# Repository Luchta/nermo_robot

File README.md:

# nermo_robot
 Hardware repository with all necessary files to build the NeRmo robot.

## DISCLAIMER

 This submission is to be used within the general terms of service of the Human Brain Project (HBP). In particular, users should not download the following code if they intend to make a military use of it.

## Repository Structure
* 3D Printing
	* STL_Files
	* Parts List
* Electronics
	* Eagle Files
	* Parts List
* Nermo User Manual.pdf
* README.md
* LICENSE

## License
[GPLv3](https://fsf.org/)

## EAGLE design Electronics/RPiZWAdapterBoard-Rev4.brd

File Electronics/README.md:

# nermo_robot
 Electronics Subfolder

## Custom PCBs

* LegSensorBoard
* RPiZWAdapterBoard
* ServoBoard
* Wire_Distr

## License
[GPLv3](https://fsf.org/)

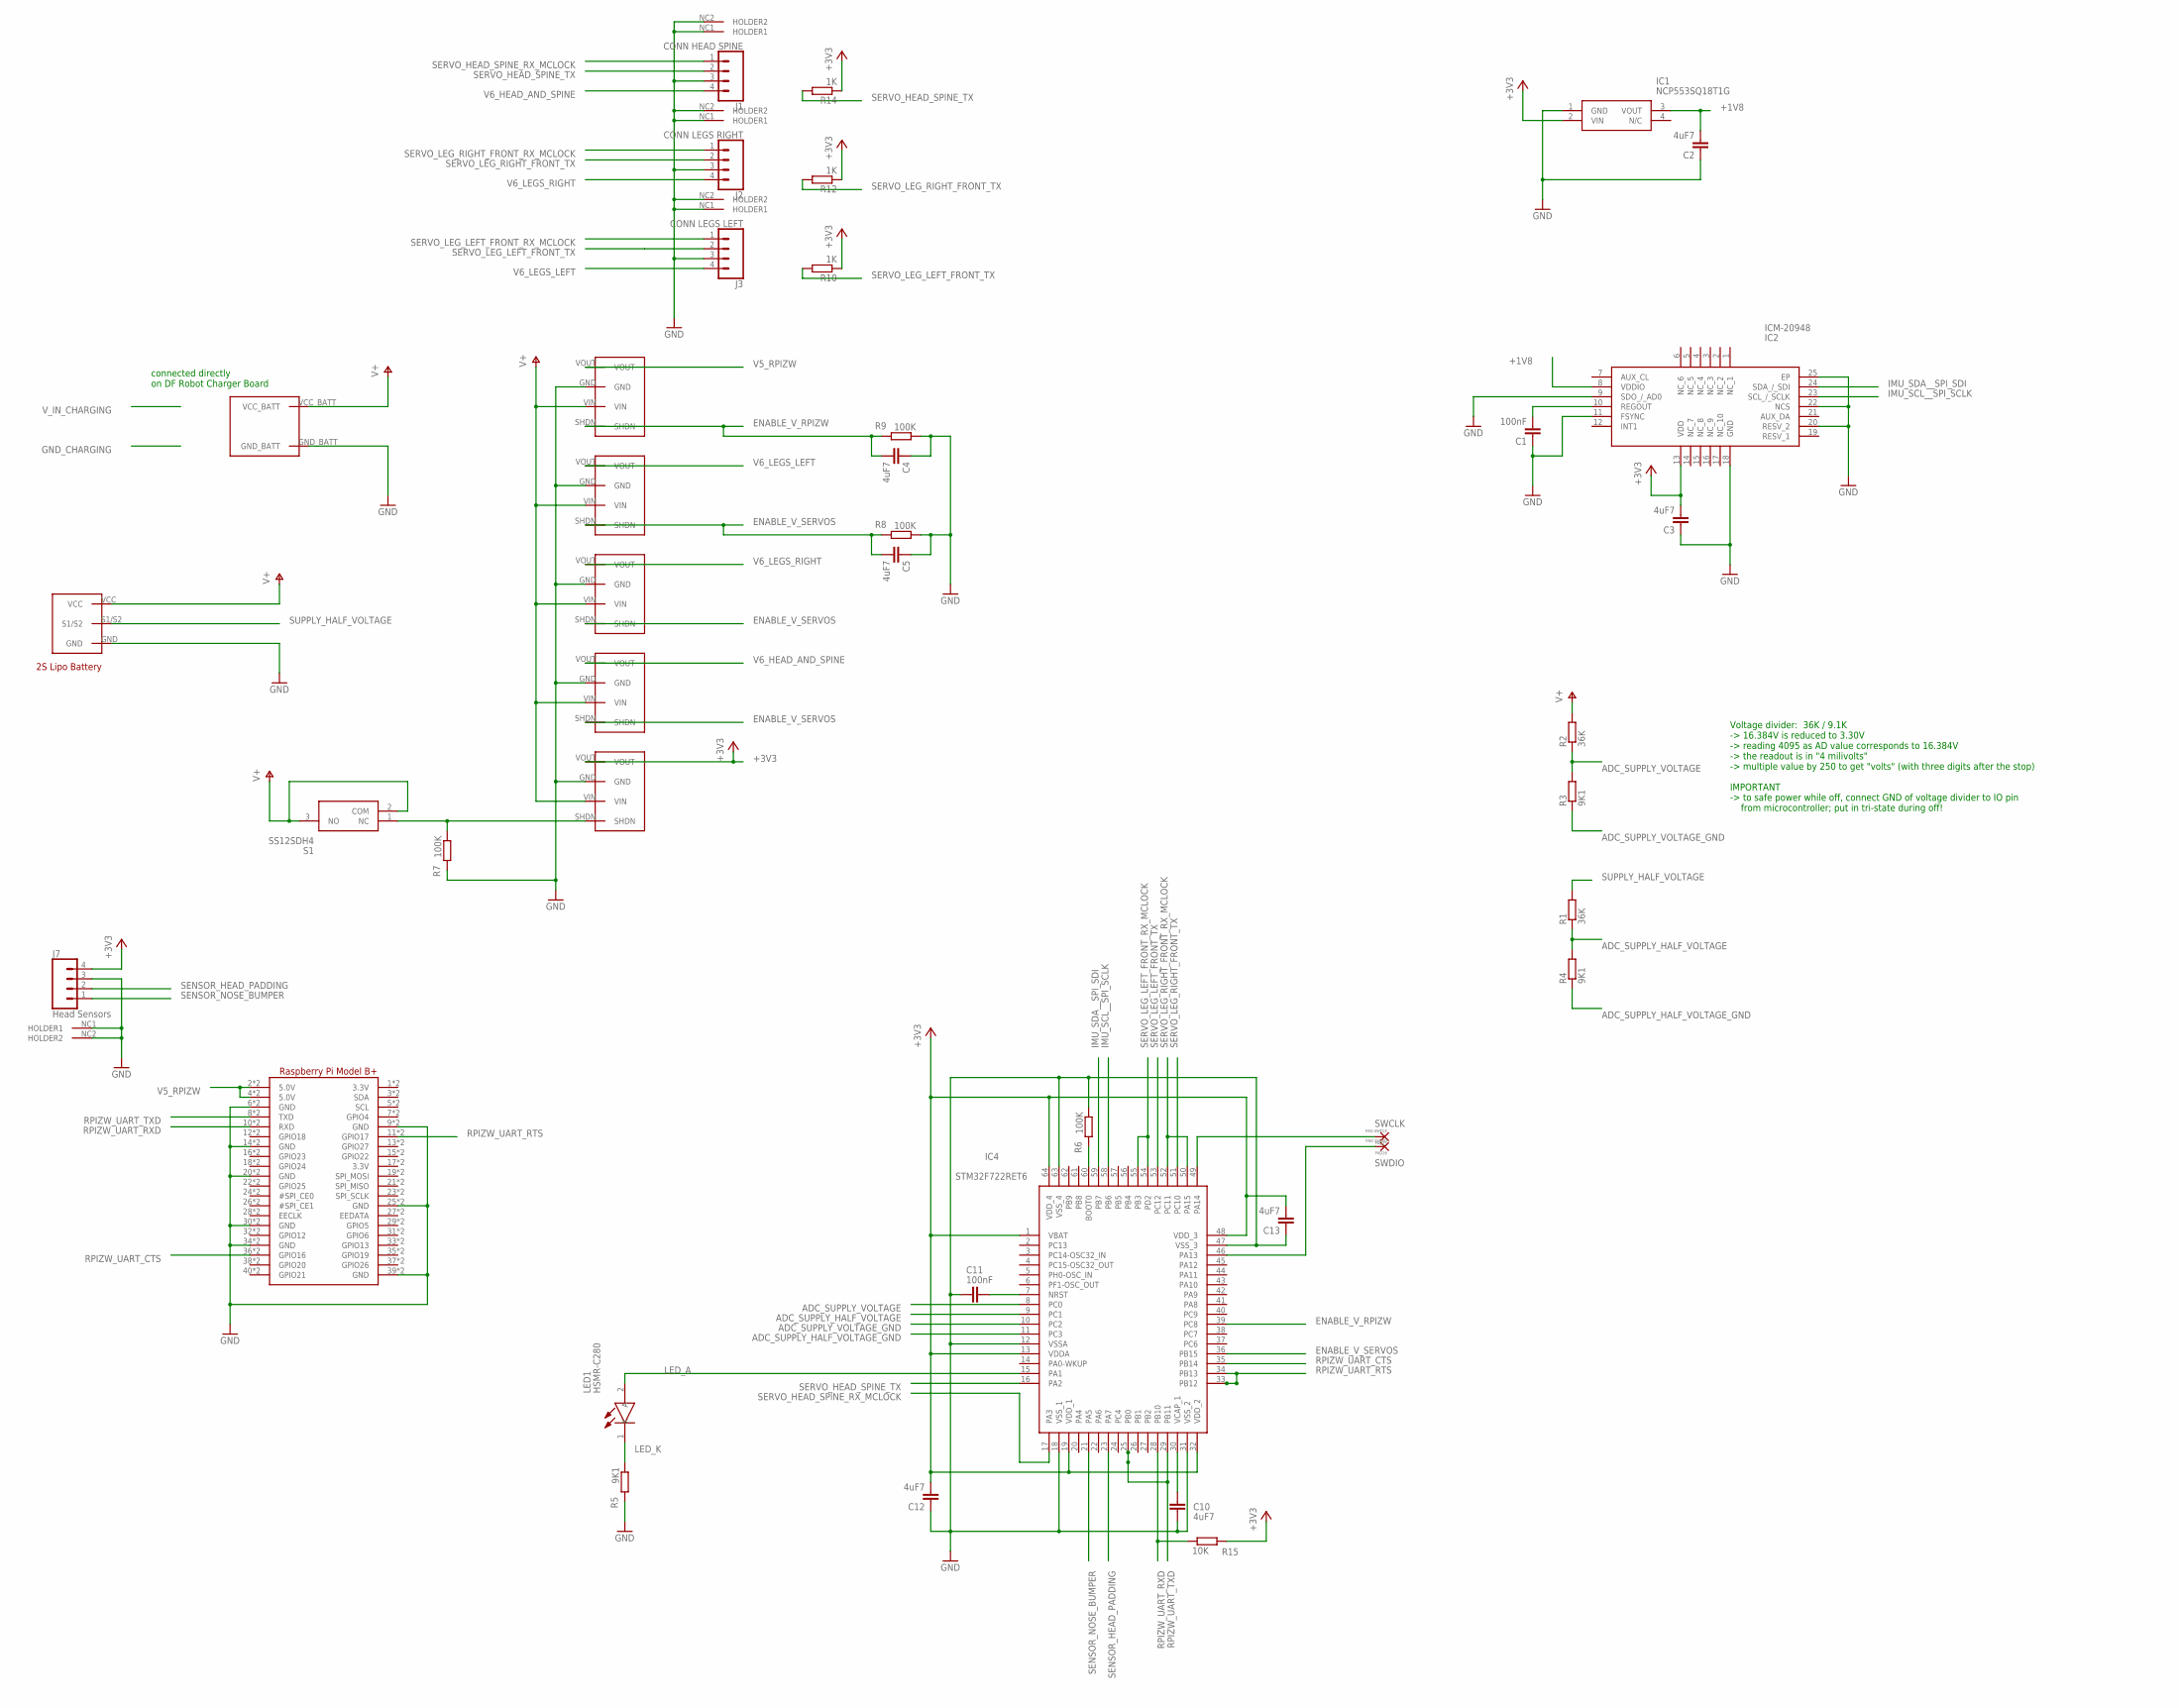
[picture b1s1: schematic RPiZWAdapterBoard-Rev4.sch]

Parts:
C1, C11: 100nF; C0402
C2, C3, C4, C5, C10, C12, C13: 4uF7; C0402
IC1: NCP553SQ18T1G; NCP563SQ18T1G
IC2: ICM-20948; QFN40P300X300X105-25N
IC4: STM32F722RET6; QFP50P1200X1200X160-64N
J1: CONN HEAD SPINE; JST04_SH_1MM
J2: CONN LEGS RIGHT; JST04_SH_1MM
J3: CONN LEGS LEFT; JST04_SH_1MM
J7: Head Sensors; JST04_SH_1MM
LED1: HSMR-C280; LEDC1005X50N
PAD25: PAD SWCLK; SMD12X08
PAD26: PAD SWDIO; SMD12X08
R1, R2: 36K; R0402
R3, R4, R5: 9K1; R0402
R6, R7, R8, R9: 100K; R0402
R10, R12, R14: 1K; R0402
R15: 10K; R0402
RPI1: MICROBUILDER_RASPBERRYPI_BPLUSWIDE; MICROBUILDER_PI_BONNET_THMSMT_WIDE
S1: SS12SDH4
U$1, U$3, U$4, U$5, U$6: POLOLU_REGULATOR
U$7: JST-S3B-XH-A_BATTCON; JST-S3B-XH-A
U$8: DFROBOT_CHARGER_CUTOUTNARROW; DFROBOT_CHARGER_CUTOUT_NARROW

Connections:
+1V8: C2.2, IC1.3 (VOUT), IC2.8 (VDDIO)
+3V3: C3.2, C12.2, C13.2, IC1.2 (VIN), IC2.13 (VDD), IC4.1 (VBAT), IC4.13 (VDDA), IC4.19 (VDD_1), IC4.32 (VDD_2), IC4.48 (VDD_3), IC4.64 (VDD_4), J7.4, R10.1, R12.1, R14.1, R15.2, U$6.VOUT
ADC_SUPPLY_HALF_VOLTAGE: IC4.9 (PC1), R1.1, R4.2
ADC_SUPPLY_HALF_VOLTAGE_GND: IC4.11 (PC3), R4.1
ADC_SUPPLY_VOLTAGE: IC4.8 (PC0), R2.1, R3.2
ADC_SUPPLY_VOLTAGE_GND: IC4.10 (PC2), R3.1
ENABLE_V_RPIZW: C4.2, IC4.39 (PC8), R9.2, U$1.SHDN
ENABLE_V_SERVOS: C5.2, IC4.36 (PB15), R8.2, U$3.SHDN, U$4.SHDN, U$5.SHDN
GND: C1.1, C2.1, C3.1, C4.1, C5.1, C10.1, C11.2, C12.1, C13.1, IC1.1 (GND), IC2.9 (SDO_/_AD0), IC2.11 (FSYNC), IC2.18 (GND), IC2.20 (RESV_2), IC2.22 (NCS), IC2.25 (EP), IC4.12 (VSSA), IC4.18 (VSS_1), IC4.31 (VSS_2), IC4.47 (VSS_3), IC4.63 (VSS_4), J1.3, J1.NC1 (HOLDER1), J1.NC2 (HOLDER2), J2.3, J2.NC1 (HOLDER1), J2.NC2 (HOLDER2), J3.3, J3.NC1 (HOLDER1), J3.NC2 (HOLDER2), J7.3, J7.NC1 (HOLDER1), J7.NC2 (HOLDER2), R5.2, R6.1, R7.2, R8.1, R9.1, RPI1.6 (GND), RPI1.9 (GND), RPI1.14 (GND), RPI1.20 (GND), RPI1.25 (GND), RPI1.30 (GND), RPI1.34 (GND), RPI1.39 (GND), RPI1.S6 (GND), RPI1.S9 (GND), RPI1.S14 (GND), RPI1.S20 (GND), RPI1.S25 (GND), RPI1.S30 (GND), RPI1.S34 (GND), RPI1.S39 (GND), U$1.GND, U$3.GND, U$4.GND, U$5.GND, U$6.GND, U$7.GND, U$8.GND_BATT
IMU_SCL__SPI_SCLK: IC2.23 (SCL_/_SCLK), IC4.58 (PB6)
IMU_SDA__SPI_SDI: IC2.24 (SDA_/_SDI), IC4.59 (PB7)
LED_A: IC4.15 (PA1), LED1.2 (A)
LED_K: LED1.1 (K), R5.1
unnamed: R7.1, S1.1 (NC), U$6.SHDN
unnamed: C1.2, IC2.10 (REGOUT)
unnamed: IC4.60 (BOOT0), R6.2
unnamed: C11.1, IC4.7 (NRST)
unnamed: C10.2, IC4.30 (VCAP_1)
RPIZW_UART_CTS: IC4.35 (PB14), RPI1.36 (GPIO16), RPI1.S36 (GPIO16)
RPIZW_UART_RTS: IC4.33 (PB12), IC4.34 (PB13), RPI1.11 (GPIO17), RPI1.S11 (GPIO17)
RPIZW_UART_RXD: IC4.28 (PB10), R15.1, RPI1.10 (RXD), RPI1.S10 (RXD)
RPIZW_UART_TXD: IC4.25 (PB0), IC4.29 (PB11), RPI1.8 (TXD), RPI1.S8 (TXD)
SENSOR_HEAD_PADDING: IC4.23 (PA7), J7.2
SENSOR_NOSE_BUMPER: IC4.21 (PA5), J7.1
SERVO_HEAD_SPINE_RX_MCLOCK: IC4.17 (PA3), J1.1
SERVO_HEAD_SPINE_TX: IC4.16 (PA2), J1.2, R14.2
SERVO_LEG_LEFT_FRONT_RX_MCLOCK: IC4.54 (PD2), IC4.55 (PB3), J3.1
SERVO_LEG_LEFT_FRONT_TX: IC4.53 (PC12), J3.2, R10.2
SERVO_LEG_RIGHT_FRONT_RX_MCLOCK: IC4.50 (PA15), IC4.52 (PC11), J2.1
SERVO_LEG_RIGHT_FRONT_TX: IC4.51 (PC10), J2.2, R12.2
SUPPLY_HALF_VOLTAGE: R1.2, U$7.S1/S2
SWCLK: IC4.49 (PA14), PAD25.1
SWDIO: IC4.46 (PA13), PAD26.1
V5_RPIZW: RPI1.2 (5.0V), RPI1.4 (5.0V), RPI1.S2 (5.0V), RPI1.S4 (5.0V), U$1.VOUT
V6_HEAD_AND_SPINE: J1.4, U$5.VOUT
V6_LEGS_LEFT: J3.4, U$3.VOUT
V6_LEGS_RIGHT: J2.4, U$4.VOUT
V+: R2.2, S1.2 (COM), S1.3 (NO), U$1.VIN, U$3.VIN, U$4.VIN, U$5.VIN, U$6.VIN, U$7.VCC, U$8.VCC_BATT

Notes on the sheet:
Voltage divider: 36K / 9.1K -> 16.384V is reduced to 3.30V -> reading 4095 as AD value corresponds to 16.384V -> the readout is in "4 milivolts" -> multiple value by 250 to get "volts" (with three digits after the stop) IMPORTANT -> to safe power while off, connect GND of voltage divider to IO pin 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
connected directly on DF Robot Charger Board

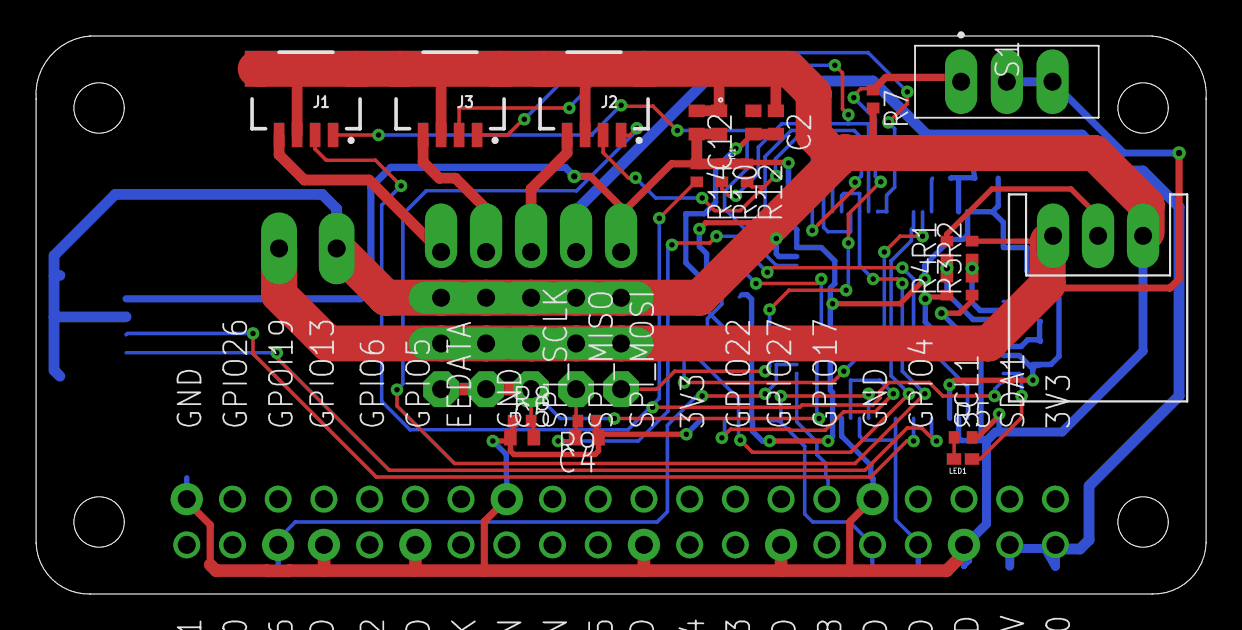
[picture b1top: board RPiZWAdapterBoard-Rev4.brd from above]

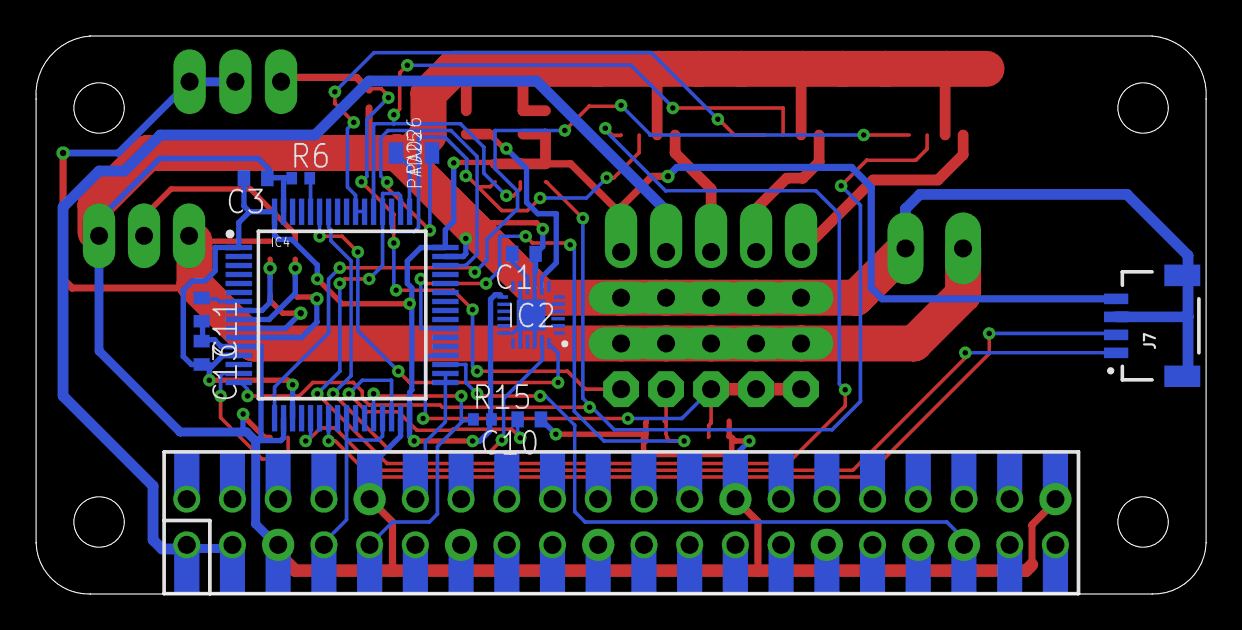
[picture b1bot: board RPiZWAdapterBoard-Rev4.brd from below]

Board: 2 copper layers, 65.0 x 31.0 mm, 41 parts (14 on the bottom side), 38 nets.

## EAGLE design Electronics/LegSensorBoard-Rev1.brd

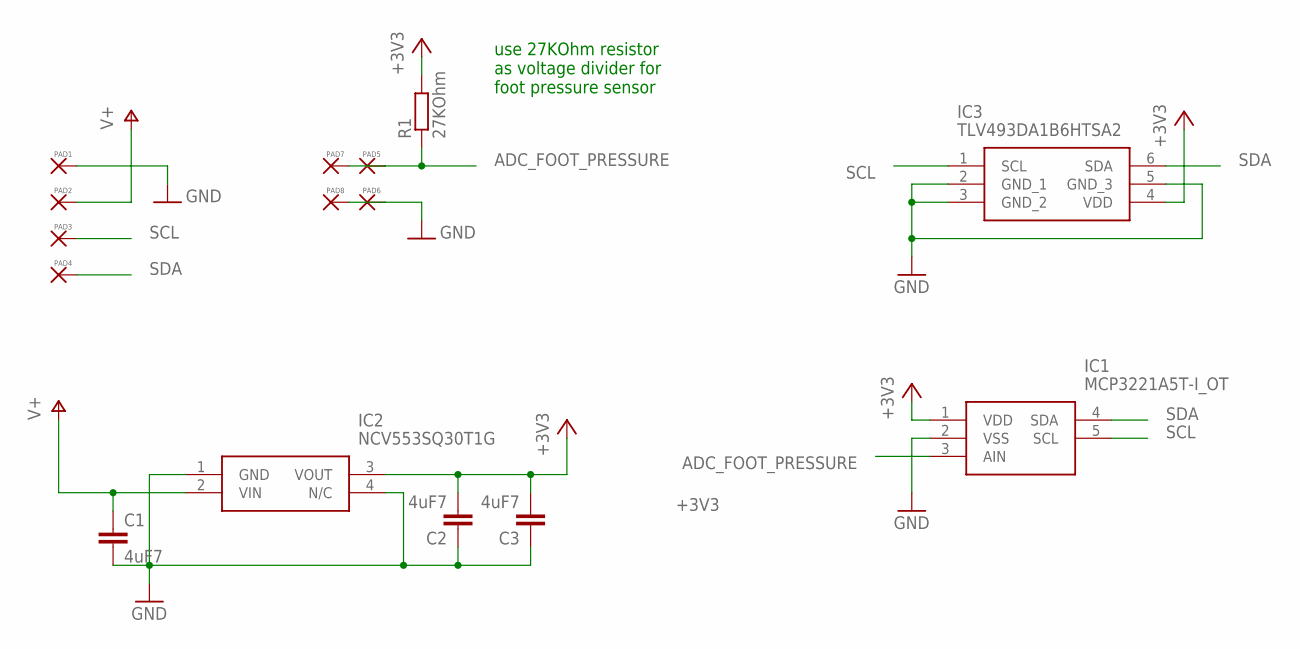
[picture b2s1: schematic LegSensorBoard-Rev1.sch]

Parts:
C1, C2, C3: 4uF7; C0402
IC1: MCP3221A5T-I_OT; SOT95P270X145-5N
IC2: NCV553SQ30T1G; NCP563SQ18T1G
IC3: TLV493DA1B6HTSA2; SOT95P250X110-6N
PAD1, PAD2, PAD3, PAD4: SMD-PAD20X07; SMD20X07
PAD5, PAD6, PAD7, PAD8: SMD-PAD14X08; SMD14X08
R1: 27KOhm; R0402

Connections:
+3V3: C2.2, C3.2, IC1.1 (VDD), IC2.3 (VOUT), IC3.4 (VDD), R1.2
ADC_FOOT_PRESSURE: IC1.3 (AIN), PAD5.1, PAD7.1, R1.1
GND: C1.2, C2.1, C3.1, IC1.2 (VSS), IC2.1 (GND), IC2.4 (N/C), IC3.2 (GND_1), IC3.3 (GND_2), IC3.5 (GND_3), PAD1.1, PAD6.1, PAD8.1
SCL: IC1.5 (SCL), IC3.1 (SCL), PAD3.1
SDA: IC1.4 (SDA), IC3.6 (SDA), PAD4.1
V+: C1.1, IC2.2 (VIN), PAD2.1

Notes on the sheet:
use 27KOhm resistor as voltage divider for foot pressure sensor

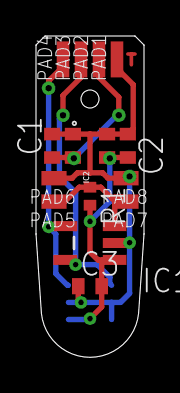
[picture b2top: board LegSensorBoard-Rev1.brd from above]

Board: 2 copper layers, 6.0 x 17.8 mm, 15 parts (1 on the bottom side), 6 nets.

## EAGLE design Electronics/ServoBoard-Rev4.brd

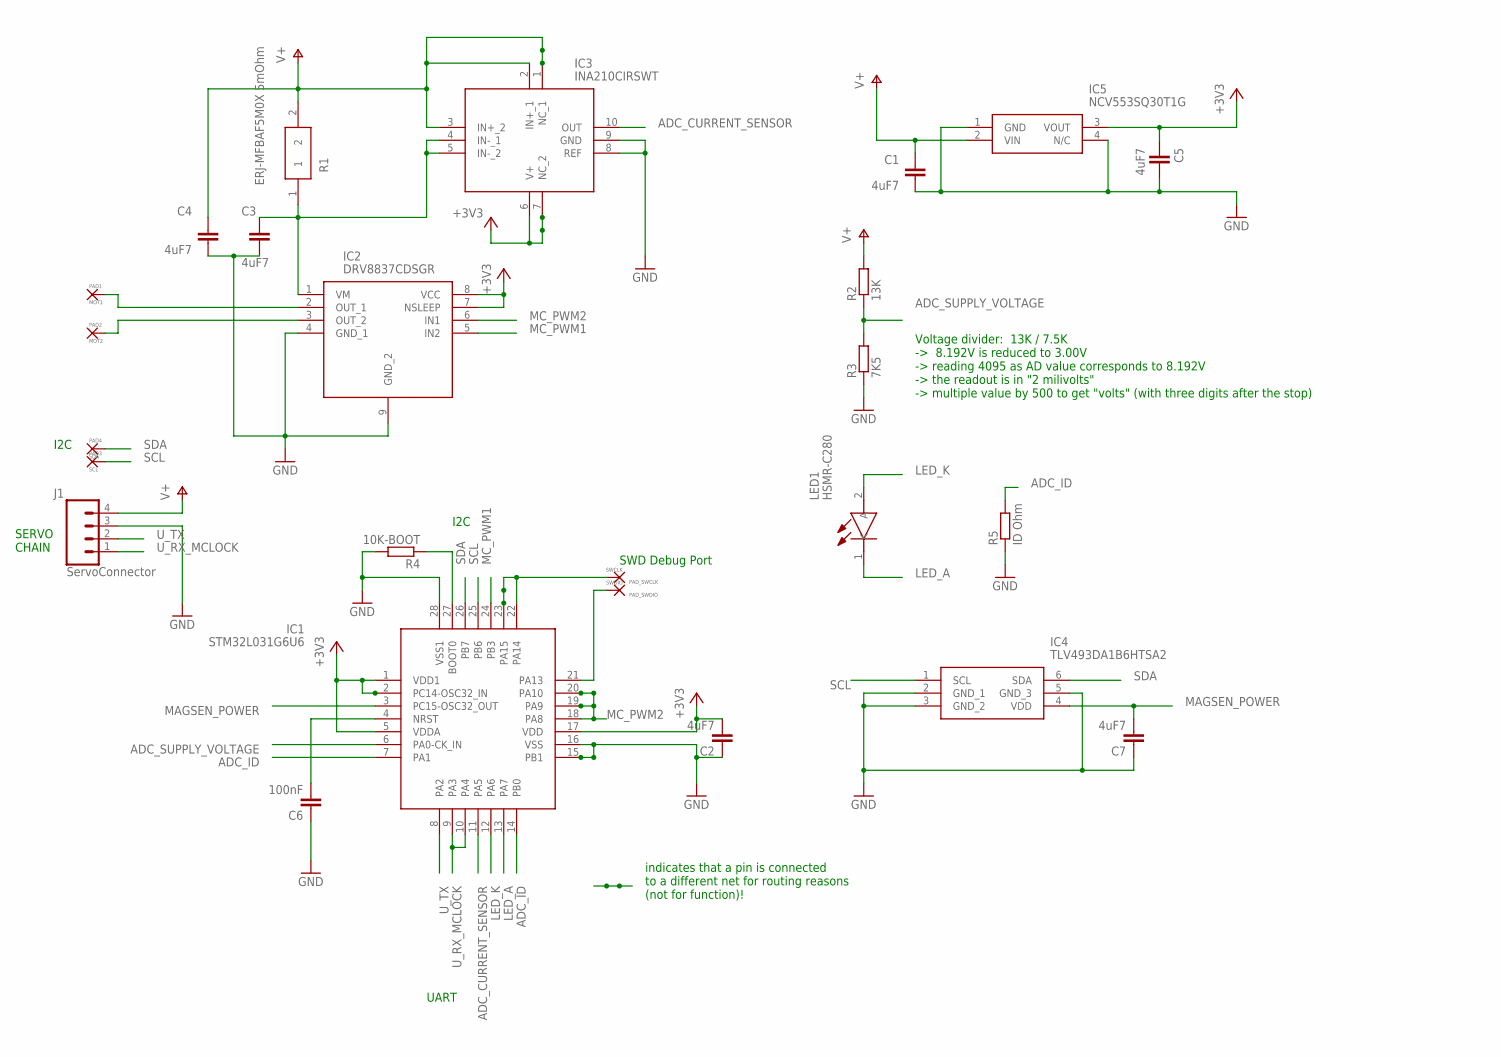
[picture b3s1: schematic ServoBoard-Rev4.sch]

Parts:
C1, C2, C3, C4, C5, C7: 4uF7; C0402
C6: 100nF; C0201
IC1: STM32L031G6U6; QFN50P400X400X60-28N
IC2: DRV8837CDSGR; SON50P200X200X80-9N
IC3: INA210CIRSWT; QFN40P140X180X55-10N
IC4: TLV493DA1B6HTSA2; SOT95P250X110-6N
IC5: NCV553SQ30T1G; NCP563SQ18T1G
J1: ServoConnector; JST04_SH_1MM
LED1: HSMR-C280; LEDC1005X50N
PAD1: MOT1; SMD12X07
PAD2: MOT2; SMD12X07
PAD3: SCL; SMD14X06
PAD4: SDA; SMD14X06
PAD_SWCLK: SWCLK; SMD06X06
PAD_SWDIO: SWDIO; SMD06X06
R1: ERJ-MFBAF5M0X 5mOhm; RESM106X40N
R2: 13K; R0402
R3: 7K5; R0402
R4: 10K-BOOT; R0402
R5: ID Ohm; R0402

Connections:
+3V3: C2.2, C5.1, IC1.1 (VDD1), IC1.2 (PC14-OSC32_IN), IC1.5 (VDDA), IC1.17 (VDD), IC2.7 (NSLEEP), IC2.8 (VCC), IC3.6 (V+), IC3.7 (NC_2), IC5.3 (VOUT)
ADC_CURRENT_SENSOR: IC1.11 (PA5), IC3.10 (OUT)
ADC_ID: IC1.7 (PA1), IC1.14 (PB0), R5.2
ADC_SUPPLY_VOLTAGE: IC1.6 (PA0-CK_IN), R2.1, R3.2
BOOT0: IC1.27 (BOOT0), R4.1
GND: C1.2, C2.1, C3.2, C4.2, C5.2, C6.1, C7.1, IC1.15 (PB1), IC1.16 (VSS), IC1.28 (VSS1), IC2.4 (GND_1), IC2.9 (GND_2), IC3.8 (REF), IC3.9 (GND), IC4.2 (GND_1), IC4.3 (GND_2), IC4.5 (GND_3), IC5.1 (GND), IC5.4 (N/C), J1.3, R3.1, R4.2, R5.1
LED_A: IC1.13 (PA7), LED1.1 (K)
LED_K: IC1.12 (PA6), LED1.2 (A)
MAGSEN_POWER: C7.2, IC1.3 (PC15-OSC32_OUT), IC4.4 (VDD)
MC_PWM1: IC1.24 (PB3), IC2.5 (IN2)
MC_PWM2: IC1.18 (PA8), IC1.19 (PA9), IC1.20 (PA10), IC2.6 (IN1)
MOTOR_1: IC2.2 (OUT_1), PAD1.1
MOTOR_2: IC2.3 (OUT_2), PAD2.1
NRST: C6.2, IC1.4 (NRST)
SCL: IC1.25 (PB6), IC4.1 (SCL), PAD3.1
SDA: IC1.26 (PB7), IC4.6 (SDA), PAD4.1
SWCLK: IC1.22 (PA14), IC1.23 (PA15), PAD_SWCLK.1
SWDIO: IC1.21 (PA13), PAD_SWDIO.1
U_RX_MCLOCK: IC1.9 (PA3), IC1.10 (PA4), J1.1
U_TX: IC1.8 (PA2), J1.2
V+: C1.1, C4.1, IC3.1 (NC_1), IC3.2 (IN+_1), IC3.3 (IN+_2), IC5.2 (VIN), J1.4, R1.2, R2.2
V_SENSOR: C3.1, IC2.1 (VM), IC3.4 (IN-_1), IC3.5 (IN-_2), R1.1

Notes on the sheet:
Voltage divider: 13K / 7.5K -> 8.192V is reduced to 3.00V -> reading 4095 as AD value corresponds to 8.192V -> the readout is in "2 milivolts" -> multiple value by 500 to get "volts" (with three digits after the stop)
SWD Debug Port
I2C
UART
SERVO CHAIN
indicates that a pin is connected to a different net for routing reasons (not for function)!

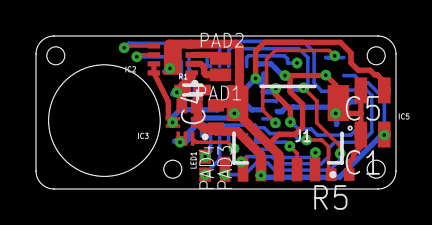
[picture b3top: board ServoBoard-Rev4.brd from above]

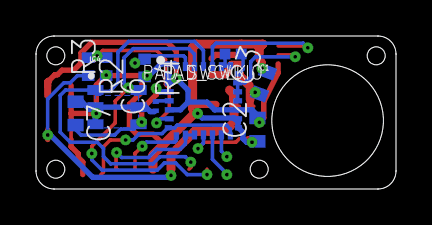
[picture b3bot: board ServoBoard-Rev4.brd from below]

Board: 2 copper layers, 20.0 x 8.5 mm, 25 parts (11 on the bottom side), 22 nets.

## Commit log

2020-03-02 STL Files inserted and renamed
2020-03-05 Updated names; included User Manual
    User manual in its first stage, only asembly instructions
2020-03-09 Manual extended, Added Electronics
    Added Leg module soldering to Manual
    Added Setup to Manual
    Added electronics files
2020-03-09 updated folders and structure
2020-03-09 updated Manuals
2020-03-13 Updated Manual, Added Firmware
